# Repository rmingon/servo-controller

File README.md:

# Dual Servo Test Board

This repository contains the design files, schematics, and PCB layout for a compact, custom-made dual-servo testing platform.
It is designed for engineers, makers, and robotics developers who need a reliable and convenient way to drive and test two RC servos simultaneously from a PC.

## Overview

This board is built around the ATmega328P microcontroller (the same MCU used in Arduino Uno), making it extremely flexible and easy to program.
Communication with the host PC is handled via an onboard CH340 UART-to-USB bridge, enabling simple plug-and-play connectivity over USB.

The board includes XT60 and XT30 connectors for safe and reliable power input, making it suitable for lab bench setups or battery-powered applications.

## Features

- Dual Servo Control  
  Two independent PWM channels allow you to control and test two RC servos simultaneously.
- Robust Power Delivery

  - XT60 and XT30 connectors for battery/power input
  - Onboard LM1117-5 voltage regulator for a stable 5V rail

- USB-to-UART Interface

  - CH340 USB-to-serial converter
  - Direct connection to PC for programming and control

- Microcontroller

  - ATmega328P running at 16 MHz
  - Fully Arduino-compatible for easy firmware development

- Test Points & Expandability
  - Breakout headers for ISP programming
  - Extra I/O pins available for debugging or future expansions

## Connectors & Interfaces

| Connector | Function                        |
| --------- | ------------------------------- |
| XT60      | Primary power input (+BAT, GND) |
| XT30      | Secondary power option          |
| USB-C     | UART communication with PC      |
| J3        | AVR-ISP programming header      |
| J4 / J5   | Servo PWM outputs               |

## Electrical Characteristics

| Parameter     | Value                      |
| ------------- | -------------------------- |
| Input Voltage | 6 – 12 V (recommended)     |
| Logic Voltage | 5 V                        |
| PWM Frequency | ~50 Hz (standard RC servo) |
| MCU Clock     | 16 MHz                     |

## Software & Usage

1. Connect Power via XT60/XT30 (or USB for low-power testing).
2. Connect to PC via USB-C cable.
3. Flash firmware using the Arduino IDE or `avrdude` over ISP.
4. Use the provided PC software or your own serial commands to control PWM output and test servo movement.

## Project Files

This repository contains:

- KiCad PCB Layout (`hardware.kicad_pcb`)
- Schematic (`hardware.kicad_sch`)
- Project Configuration Files (`.kicad_pro`, `.kicad_prl`)
- 3D Render and PCB previews

## Applications

- Servo quality testing (batch verification)
- Robotics development and debugging
- Educational tools for learning PWM and MCU programming
- Rapid prototyping for motion-control projects

## Future Improvements

- Add current sensing for each servo channel
- Optional I²C/UART expansion for external sensors
- Integrate reverse-polarity protection on power input

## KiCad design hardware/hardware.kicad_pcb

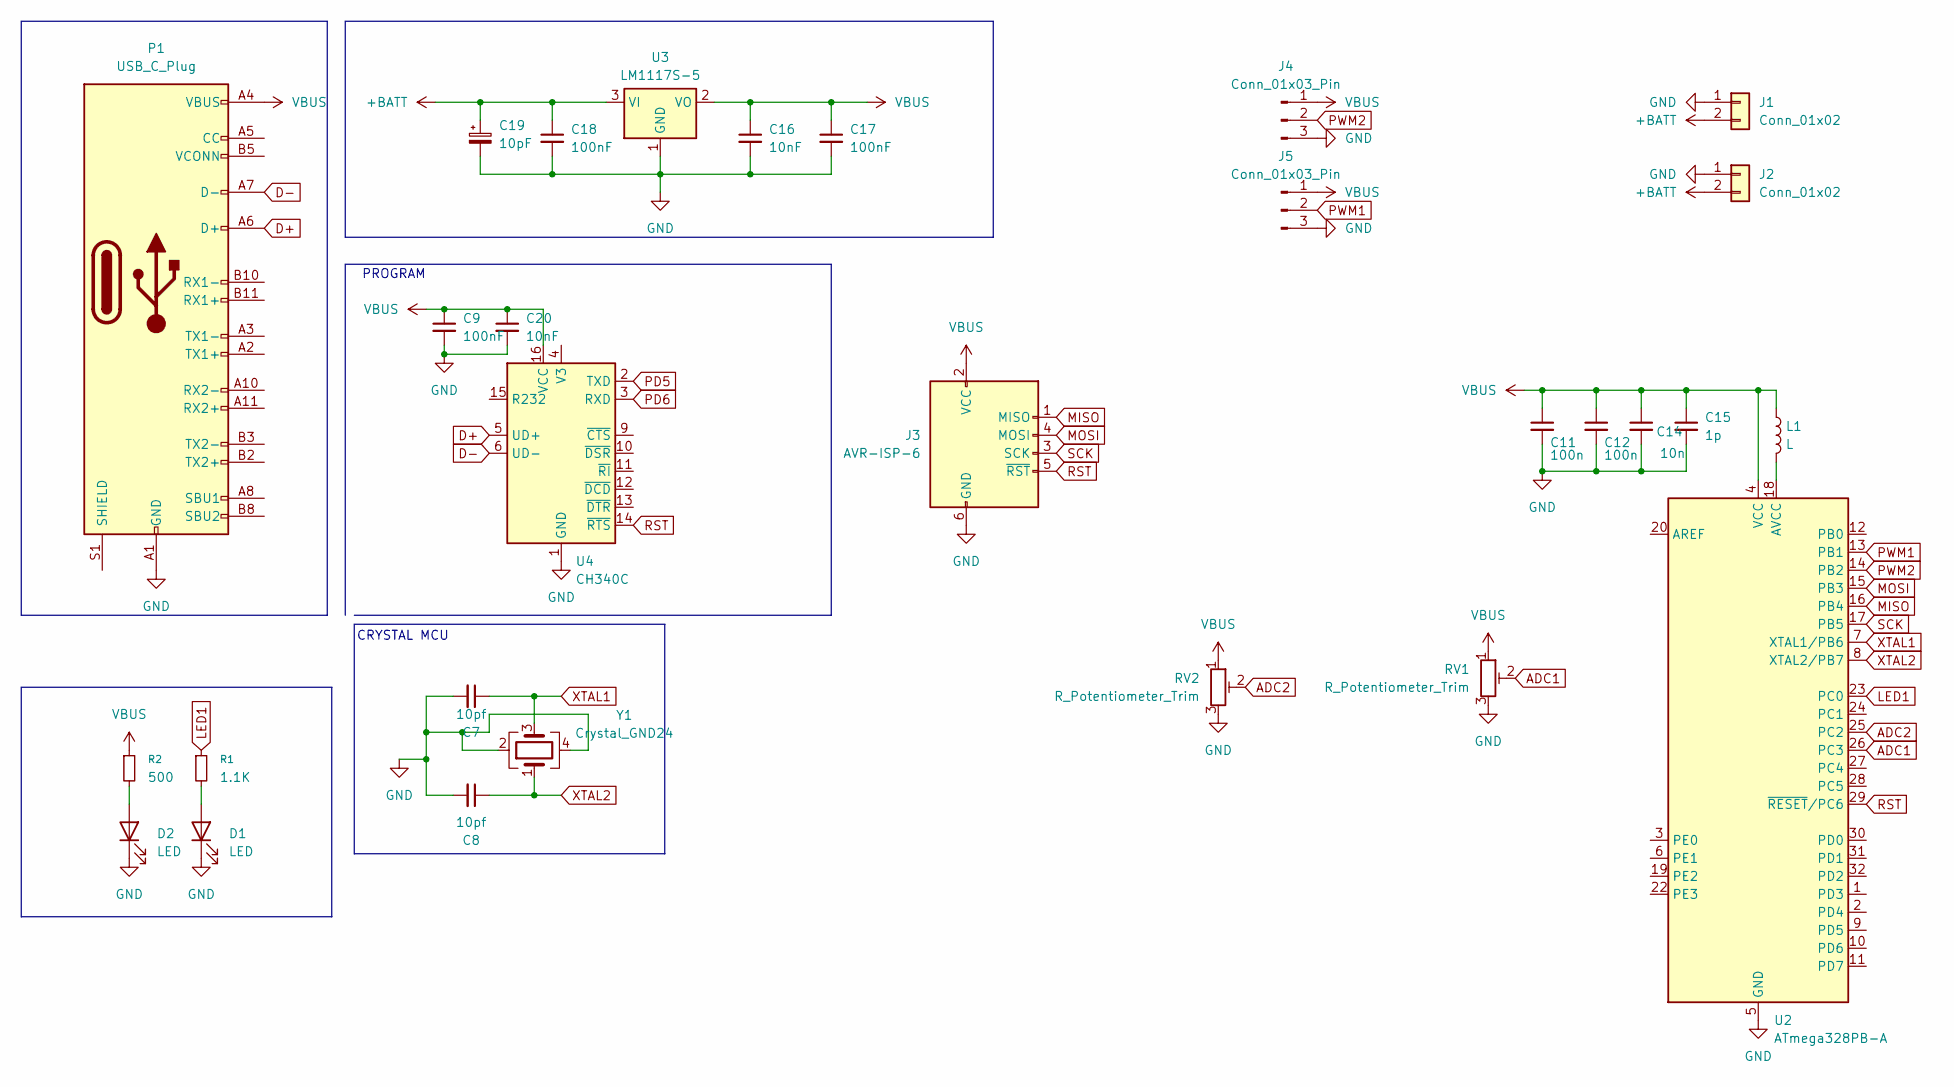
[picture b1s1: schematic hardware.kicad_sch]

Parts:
C7, C8: 10pf; C_0603_1608Metric; LCSC C106245
C9, C17, C18: 100nF; C_0603_1608Metric
C11, C12: 100n; C_0603_1608Metric
C14: 10n; C_0603_1608Metric
C15: 1p; C_0603_1608Metric
C16, C20: 10nF; C_0603_1608Metric
C19: 10pF; C_Elec_3x5.4
D1, D2: LED; LED_0603_1608Metric
J1: Conn_01x02; AMASS_XT60-F_1x02_P7.20mm_Vertical
J2: Conn_01x02; AMASS_XT30U-F_1x02_P5.0mm_Vertical
J3: AVR-ISP-6; PinHeader_2x03_P2.54mm_Vertical
J4, J5: Conn_01x03_Pin; PinHeader_1x03_P2.54mm_Vertical
L1: L; L_0603_1608Metric
P1: USB_C_Plug; USB_C_Receptacle_GCT_USB4105-xx-A_16P_TopMnt_Horizontal
R1: 1.1K; R_0603_1608Metric
R2: 500; R_0603_1608Metric
RV1, RV2: R_Potentiometer_Trim; Potentiometer_Runtron_RM-065_Vertical
U2: ATmega328PB-A; TQFP-32_7x7mm_P0.8mm
U3: LM1117S-5; SOT-223-3_TabPin2
U4: CH340C; SOIC-16_3.9x9.9mm_P1.27mm
Y1: Crystal_GND24; Crystal_SMD_3225-4Pin_3.2x2.5mm

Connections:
+BATT: C18.1, C19.1, J1.2, J2.2, U3.3 (VI)
ADC1: RV1.2, U2.26 (PC3)
ADC2: RV2.2, U2.25 (PC2)
D+: P1.A6 (D+), U4.5 (UD+)
D-: P1.A7 (D-), U4.6 (UD-)
GND: C7.2, C8.2, C9.2, C11.2, C12.2, C14.2, C15.2, C16.2, C17.2, C18.2, C19.2, C20.2, D1.1 (K), D2.1 (K), J1.1, J2.1, J3.6 (GND), J4.3, J5.3, P1.A1 (GND), P1.A12 (GND), P1.B1 (GND), P1.B12 (GND), RV1.3, RV2.3, U2.5 (GND), U2.21 (GND), U3.1 (GND), U4.1 (GND), Y1.2, Y1.4
LED1: R1.1, U2.23 (PC0)
MISO: J3.1 (MISO), U2.16 (PB4)
MOSI: J3.4 (MOSI), U2.15 (PB3)
unnamed: D1.2 (A), R1.2
unnamed: D2.2 (A), R2.2
unnamed: L1.2, U2.18 (AVCC)
PD5: U4.2 (TXD)
PD6: U4.3 (RXD)
PWM1: J5.2, U2.13 (PB1)
PWM2: J4.2, U2.14 (PB2)
RST: J3.5 (~RST), U2.29 (~RESET/PC6), U4.14 (~RTS)
SCK: J3.3 (SCK), U2.17 (PB5)
VBUS: C9.1, C11.1, C12.1, C14.1, C15.1, C16.1, C17.1, C20.1, J3.2 (VCC), J4.1, J5.1, L1.1, P1.A4 (VBUS), P1.A9 (VBUS), P1.B4 (VBUS), P1.B9 (VBUS), R2.1, RV1.1, RV2.1, U2.4 (VCC), U3.2 (VO), U4.16 (VCC)
XTAL1: C7.1, U2.7 (XTAL1/PB6), Y1.3
XTAL2: C8.1, U2.8 (XTAL2/PB7), Y1.1

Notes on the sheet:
PROGRAM
CRYSTAL MCU

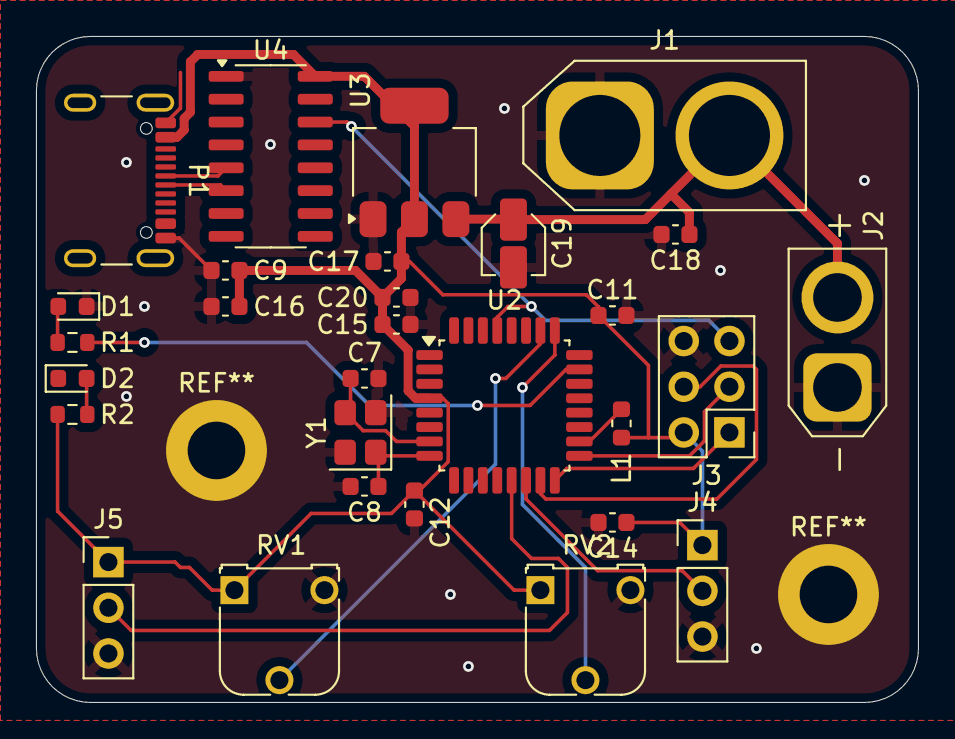
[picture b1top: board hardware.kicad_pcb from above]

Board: 2 copper layers, 49.0 x 37.0 mm, 29 parts (0 on the bottom side), 19 nets.

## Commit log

2025-09-14 minimal schematic
2025-09-14 add qfn32 atmega
2025-09-14 add isp connector
2025-09-14 finish schematic
2025-09-14 pcb wiring
2025-09-14 add pictures
2025-09-14 add readme
2025-09-14 add picutes
